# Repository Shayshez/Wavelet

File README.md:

# Wavelet
## CC-BY-SA 4.0
Rotatable multimode filter based on MI "Ripples"

## ROTATABLE = Modules for 3u / 1u
Wavelet comes with 2 panels: 1u/20hp and 3u/6hp

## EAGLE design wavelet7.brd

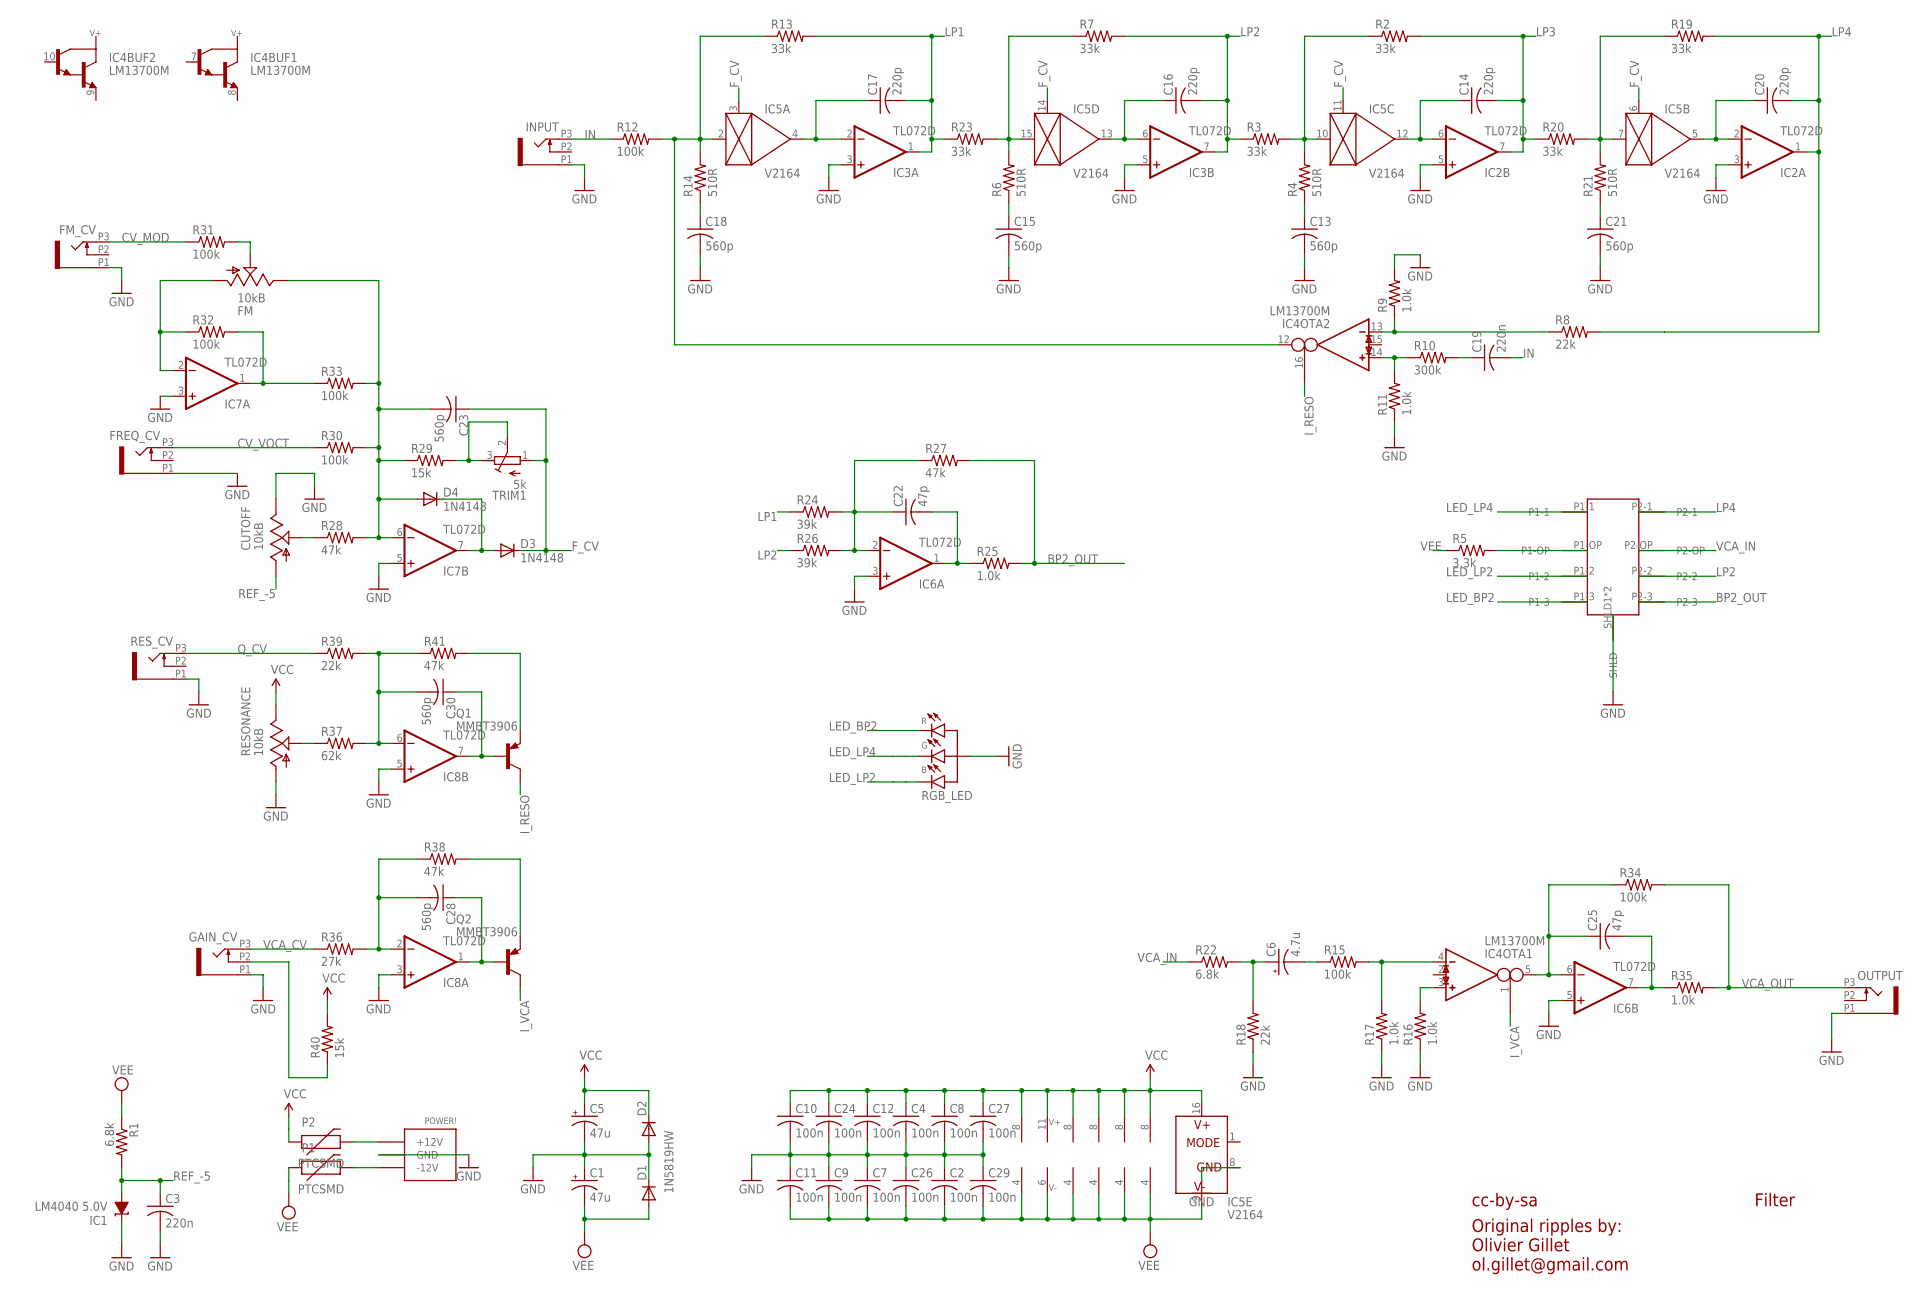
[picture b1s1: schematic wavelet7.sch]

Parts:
C1, C5: 47u; PANASONIC_D
C2, C4, C7, C8, C9, C10, C11, C12, C24, C26, C27, C29: 100n; C0603
C3, C19: 220n; C0603
C6: 4.7u; PANASONIC_B
C13, C15, C18, C21, C23, C28, C30: 560p; C0603
C14, C16, C17, C20: 220p; C0603
C22, C25: 47p; C0603
CUTOFF: 10kB; ALPS_POT_VERTICAL_PS
D1, D2: 1N5819HW; SOD123
D3, D4: 1N4148; SOD323-W
FILTER_MODE: APEM-MHS233K
FM: 10kB; ALPS_POT_VERTICAL_PS
FM_CV: OG-PJ301_PJ301_THONKICONN; OG-PJ301_WQP_PJ_301M6_NO_HOLE
FREQ_CV: OG-PJ301_PJ301_THONKICONN; OG-PJ301_WQP_PJ_301M6_NO_HOLE
GAIN_CV: OG-PJ301_PJ301_THONKICONN; OG-PJ301_WQP_PJ_301M6_NO_HOLE
IC1: LM4040 5.0V; DBZ_R-PDSO-G3
IC2, IC3, IC6, IC7, IC8: TL072D; SO08
IC4: LM13700M; SO16
IC5: V2164; SOIC16N
INPUT: OG-PJ301_PJ301_THONKICONN; OG-PJ301_WQP_PJ_301M6_NO_HOLE
OUTPUT: OG-PJ301_PJ301_THONKICONN; OG-PJ301_WQP_PJ_301M6_NO_HOLE
P1, P2: PTCSMD; PTC-1206
POWER!: POWER_SIMPLE; 2X05_SMT_HEADER
Q1, Q2: MMBT3906; SOT23-BEC
R1, R22: 6.8k; R0603
R2, R3, R7, R13, R19, R20, R23: 33k; R0603
R4, R6, R14, R21: 510R; R0603
R5: 3.3k; R0603
R8, R18, R39: 22k; R0603
R9, R11, R16, R17, R25, R35: 1.0k; R0603
R10: 300k; R0603
R12, R15, R30, R31, R32, R33, R34: 100k; R0603
R24, R26: 39k; R0603
R27, R28, R38, R41: 47k; R0603
R29, R40: 15k; R0603
R36: 27k; R0603
R37: 62k; R0603
RESONANCE: 10kB; ALPS_POT_VERTICAL_PS
RES_CV: OG-PJ301_PJ301_THONKICONN; OG-PJ301_WQP_PJ_301M6_NO_HOLE
RGB_LED: LED-RGB-CA-HEBEI; PLCC4
TRIM1: 5k; RTRIM3296X

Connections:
BP2_OUT: FILTER_MODE.P2-3, R25.2, R27.2
CV_F_POT: CUTOFF.P$2 (S), R28.1
CV_MOD: FM_CV.P3 (3), R31.1
CV_VOCT: FREQ_CV.P3 (3), R30.1
F_CV: C23.1, D3.C, IC5.3 (CTRL), IC5.6 (CTRL), IC5.11 (CTRL), IC5.14 (CTRL), TRIM1.1 (E)
GND: C1.+, C2.1, C3.2, C4.2, C5.-, C7.1, C8.2, C9.1, C10.2, C11.1, C12.2, C13.2, C15.2, C18.2, C21.2, C24.2, C26.1, C27.2, C29.1, CUTOFF.P$1 (E), D1.C, D2.A, FILTER_MODE.SHLD1 (SHLD), FILTER_MODE.SHLD2 (SHLD), FM_CV.P1 (1), FREQ_CV.P1 (1), GAIN_CV.P1 (1), IC1.1 (C), IC2.3 (+IN), IC2.5 (+IN), IC3.3 (+IN), IC3.5 (+IN), IC5.8 (GND), IC6.3 (+IN), IC6.5 (+IN), IC7.3 (+IN), IC7.5 (+IN), IC8.3 (+IN), IC8.5 (+IN), INPUT.P1 (1), OUTPUT.P1 (1), POWER!.3 (GND), POWER!.4 (GND), POWER!.5 (GND), POWER!.6 (GND), POWER!.7 (GND), POWER!.8 (GND), R9.2, R11.1, R16.1, R17.1, R18.1, RESONANCE.P$3 (A), RES_CV.P1 (1), RGB_LED.P$2 (A)
IN: C19.2, INPUT.P3 (3), R12.1
I_RESO: IC4.16 (I_BIAS), Q1.C
I_VCA: IC4.1 (I_BIAS), Q2.C
LED_BP2: FILTER_MODE.P1-3, RGB_LED.P$1 (CR)
LED_LP2: FILTER_MODE.P1-2, RGB_LED.P$3 (CB)
LED_LP4: FILTER_MODE.P1-1, RGB_LED.P$4 (CG)
LP1: C17.2, IC3.1 (OUT), R13.2, R23.1, R24.1
LP2: C16.2, FILTER_MODE.P2-2, IC3.7 (OUT), R3.1, R7.2, R26.1
LP3: C14.2, IC2.7 (OUT), R2.2, R20.1
LP4: C20.2, FILTER_MODE.P2-1, IC2.1 (OUT), R8.2, R19.2
unnamed: IC7.1 (OUT), R32.2, R33.1
unnamed: C17.1, IC3.2 (-IN), IC5.4 (OUT)
unnamed: IC5.15 (IN), R6.2, R7.1, R23.2
unnamed: R29.2, TRIM1.2 (S), TRIM1.3 (A)
unnamed: IC4.3 (IN_P), R16.2
unnamed: P2.2, POWER!.9 (+12V), POWER!.10 (+12V)
unnamed: C19.1, R10.2
unnamed: C18.1, R14.1
unnamed: C16.1, IC3.6 (-IN), IC5.13 (OUT)
unnamed: IC4.12 (OUT), IC5.2 (IN), R12.2, R13.1, R14.2
unnamed: C15.1, R6.1
unnamed: IC5.10 (IN), R2.1, R3.2, R4.2
unnamed: C14.1, IC2.6 (-IN), IC5.12 (OUT)
unnamed: IC4.13 (IN_N), R8.1, R9.1
unnamed: C13.1, R4.1
unnamed: IC5.7 (IN), R19.1, R20.2, R21.2
unnamed: C20.1, IC2.2 (-IN), IC5.5 (OUT)
unnamed: IC4.14 (IN_P), R10.1, R11.2
unnamed: C21.1, R21.1
unnamed: P1.2, POWER!.1 (-12V), POWER!.2 (-12V)
unnamed: FM.P$2 (S), R31.2
unnamed: FM.P$3 (A), IC7.2 (-IN), R32.1
unnamed: C23.2, D4.A, FM.P$1 (E), IC7.6 (-IN), R28.2, R29.1, R30.2, R33.2
unnamed: R37.1, RESONANCE.P$2 (S)
unnamed: C28.2, IC8.2 (-IN), R36.2, R38.1
unnamed: C30.2, IC8.6 (-IN), R37.2, R39.2, R41.1
unnamed: C30.1, IC8.7 (OUT), Q1.B
unnamed: Q1.E, R41.2
unnamed: GAIN_CV.P2 (2), R40.1
unnamed: C28.1, IC8.1 (OUT), Q2.B
unnamed: Q2.E, R38.2
unnamed: C6.+, R18.2, R22.2
unnamed: FILTER_MODE.P1-OP, R5.2
unnamed: D3.A, D4.C, IC7.7 (OUT)
unnamed: C22.1, IC6.2 (-IN), R24.2, R26.2, R27.1
unnamed: C22.2, IC6.1 (OUT), R25.1
unnamed: IC4.4 (IN_N), R15.2, R17.2
unnamed: C25.1, IC4.5 (OUT), IC6.6 (-IN), R34.1
unnamed: C25.2, IC6.7 (OUT), R35.1
unnamed: C6.-, R15.1
Q_CV: R39.1, RES_CV.P3 (3)
REF_-5: C3.1, CUTOFF.P$3 (A), IC1.2 (A), R1.2
VCA_CV: GAIN_CV.P3 (3), R36.1
VCA_IN: FILTER_MODE.P2-OP, R22.1
VCA_OUT: OUTPUT.P3 (3), R34.2, R35.2
VCC: C4.1, C5.+, C8.1, C10.1, C12.1, C24.1, C27.1, D2.C, IC2.8 (V+), IC3.8 (V+), IC4.11 (V+), IC5.16 (V+), IC6.8 (V+), IC7.8 (V+), IC8.8 (V+), P2.1, R40.2, RESONANCE.P$1 (E)
VEE: C1.-, C2.2, C7.2, C9.2, C11.2, C26.2, C29.2, D1.A, IC2.4 (V-), IC3.4 (V-), IC4.6 (V-), IC5.9 (V-), IC6.4 (V-), IC7.4 (V-), IC8.4 (V-), P1.1, R1.1, R5.1

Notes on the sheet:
cc-by-sa
Olivier Gillet
ol.gillet@gmail.com
Filter
Original ripples by:

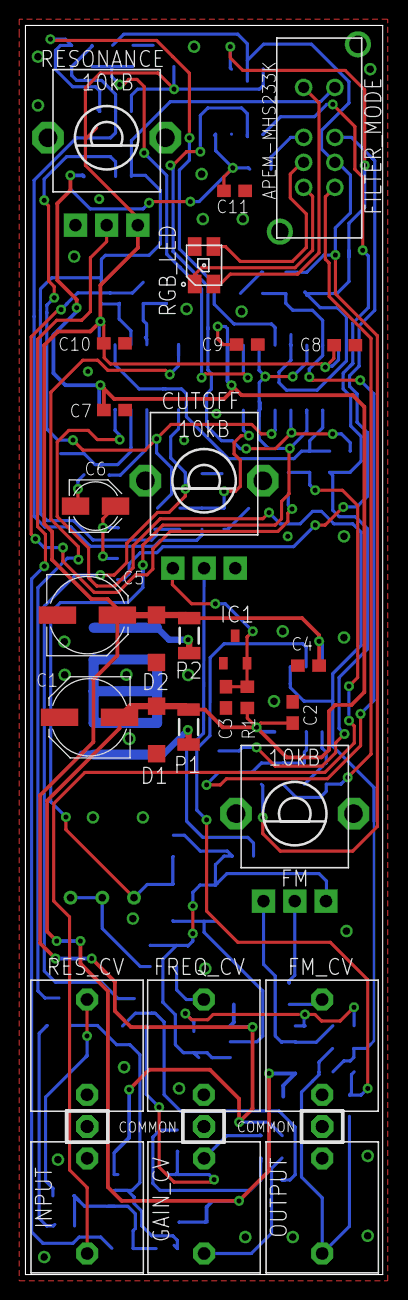
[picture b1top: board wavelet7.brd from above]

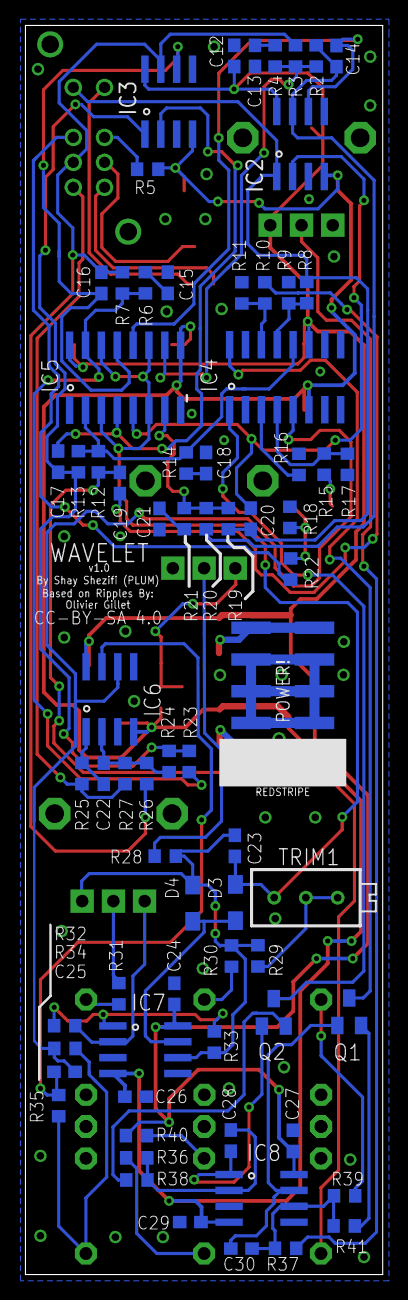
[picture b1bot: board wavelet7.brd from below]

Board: 2 copper layers, 28.6 x 100.0 mm, 100 parts (72 on the bottom side), 63 nets.

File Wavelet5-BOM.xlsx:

Qty | Value | Device | Package | Parts | Description
1 | 6.8k | R-US_R0603 | R0603 | R22 | RESISTOR, American symbol
4 | 510R | R-US_R0603 | R0603 | R4, R6, R14, R21 | RESISTOR, American symbol
6 | 1.0k | R-US_R0603 | R0603 | R9, R11, R16, R17, R25, R35 | RESISTOR, American symbol
1 | 6.8k | R-US_R0603 | R0603 | R1 | RESISTOR, American symbol
1 | 3.6k | R-US_R0603 | R0603 | R5 | RESISTOR, American symbol
2 | 15k | R-US_R0603 | R0603 | R29, R40 | RESISTOR, American symbol
3 | 22k | R-US_R0603 | R0603 | R8, R18, R39 | RESISTOR, American symbol
1 | 27k | R-US_R0603 | R0603 | R36 | RESISTOR, American symbol
7 | 33k | R-US_R0603 | R0603 | R2, R3, R7, R13, R19, R20, R23 | RESISTOR, American symbol
2 | 39k | R-US_R0603 | R0603 | R24, R26 | RESISTOR, American symbol
4 | 47k | R-US_R0603 | R0603 | R27, R28, R38, R41 | RESISTOR, American symbol
1 | 62k | R-US_R0603 | R0603 | R37 | RESISTOR, American symbol
7 | 100k | R-US_R0603 | R0603 | R12, R15, R30, R31, R32, R33, R34 | RESISTOR, American symbol
1 | 300k | R-US_R0603 | R0603 | R10 | RESISTOR, American symbol
2 | 47p | C-USC0603 | C0603 | C22, C25 | CAPACITOR, American symbol
4 | 220p | C-USC0603 | C0603 | C14, C16, C17, C20 | CAPACITOR, American symbol
7 | 560p | C-USC0603 | C0603 | C13, C15, C18, C21, C23, C28, C30 | CAPACITOR, American symbol
12 | 100n | C-USC0603 | C0603 | C2, C4, C7, C8, C9, C10, C11, C12, C24, C26, C27, C29 | CAPACITOR, American symbol
2 | 220n | C-USC0603 | C0603 | C3, C19 | CAPACITOR, American symbol
1 | 4.7u | CPOL-USB | PANASONIC_B | C6 | POLARIZED CAPACITOR, American symbol
2 | 47u | CPOL-USD | PANASONIC_D | C1, C5 | POLARIZED CAPACITOR, American symbol
2 | 1N4148 | DIODE-SOD323-W | SOD323-W | D3, D4 | DIODE
2 | 1N5819HW | DIODE-SOD123 | SOD123 | D1, D2 | DIODE
1 | LED-RGB-CA-HEBEI | LED-RGB-CA-HEBEI | PLCC4 | RGB_LED | Hebei I.T. (Shanghai) PLCC4RGBCT-CA
1 | LM13700M | LM13700M | SO16 | IC4 | Dual OTA with buffers
1 | LM4040 5.0V | LM4041C12DBZ | DBZ_R-PDSO-G3 | IC1 | PRECISION MICROPOWER SHUNT VOLTAGE REFERENCE
2 | MMBT3906 | MMBT3906LT1-PNP-SOT23-BEC | SOT23-BEC | Q1, Q2 | PNP Transistror
2 | PTCSMD | PTCSMD | PTC-1206 | P1, P2 | Resettable Fuse PTC
5 | TL072D | TL072D | SO08 | IC2, IC3, IC6, IC7, IC8 - (IC2 & IC3 PIN 1 SHOLD BE BOTTOM LEFT!) | OP AMP
1 | V2164 | SSM2164S | SOIC16N | IC5
6 | OG-PJ301_PJ301_THONKICONN | OG-PJ301_PJ301_THONKICONN | OG-PJ301_WQP_PJ_301M6_NO_HOLE | FM_CV, FREQ_CV, GAIN_CV, INPUT, OUTPUT, RES_CV
1 | POWER_SIMPLE | POWER_SIMPLE | 2X05_SMT_HEADER | POWER!
1 | 5k | R-TRIMM3296X | RTRIM3296X | TRIM1 | Trimm resistor
3 | 10kB | POT_USVERTICAL_PS | ALPS_POT_VERTICAL_PS | CUTOFF, FM, RESONANCE
1 | APEM-MHS233K | APEM-MHS233K | APEM-MHS233K | FILTER_TYPE
